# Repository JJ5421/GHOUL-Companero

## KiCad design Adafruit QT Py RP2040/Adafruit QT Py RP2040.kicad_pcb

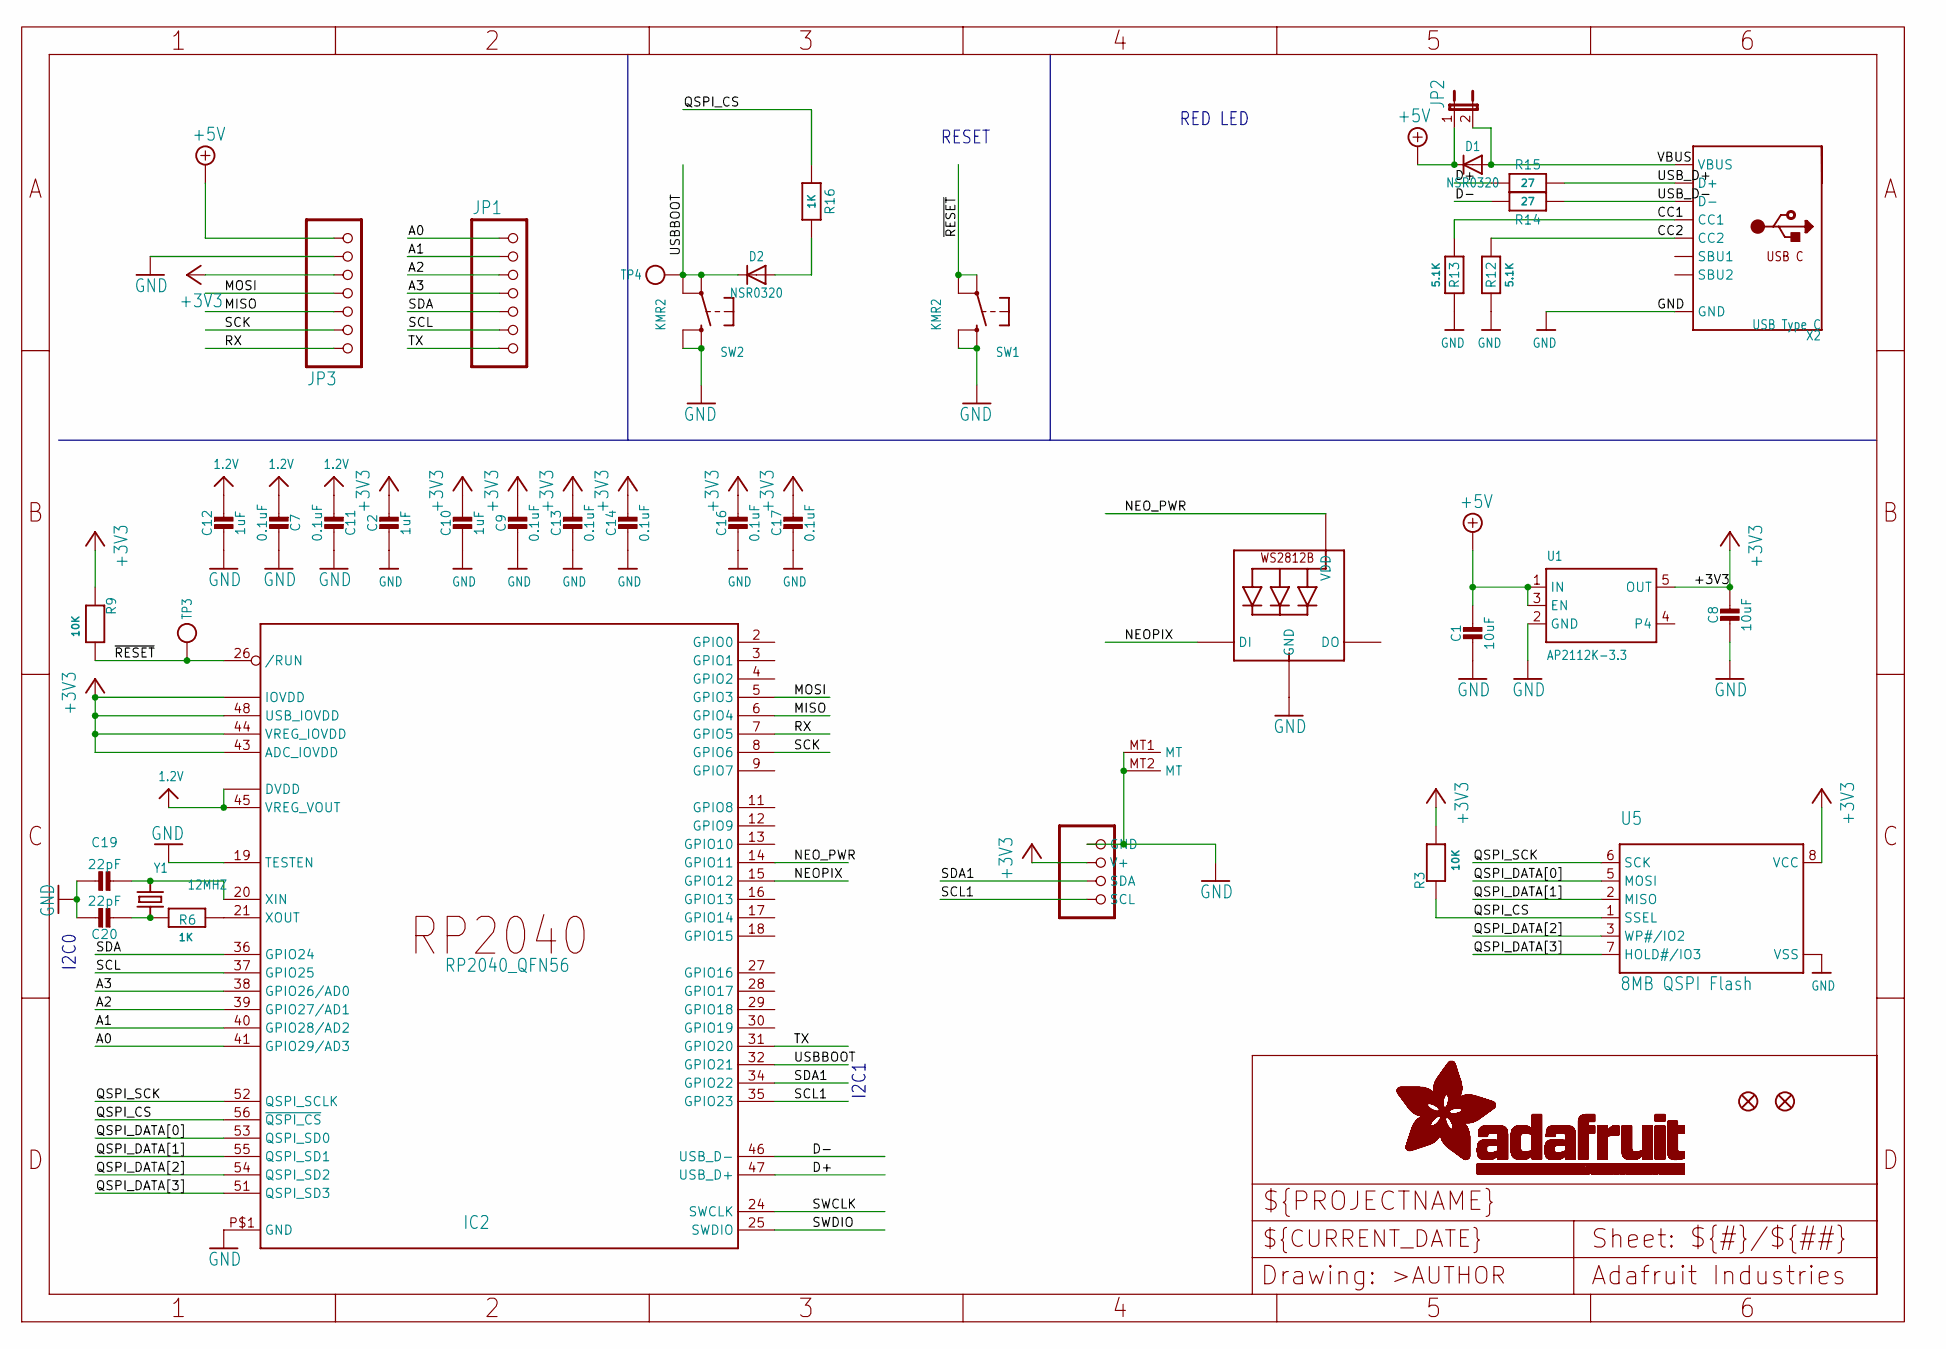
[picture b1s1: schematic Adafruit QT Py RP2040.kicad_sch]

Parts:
C1, C8: 10uF; 0805-NO
C2, C10, C12: 1uF; 0603-NO
C7, C9, C11, C13, C14, C16, C17: 0.1uF; _0402NO
C19, C20: 22pF; _0402NO
CONN1: STEMMA_I2C_QTSKINNY; JST_SH4_SKINNY
D1, D2: NSR0320; SOD-323_MINI
IC2: RP2040_QFN56; QFN56_7MM_REDUCEDEPAD
JP1, JP3: HEADER-1X7_CASTEL; 1X07_CASTEL
JP2: JUMPER-2SMD-NO; SJ_2S-NO
LED1: WS2812B_SK6805_1515; SK6805_1515
R3, R9: 10K; _0402NO
R6, R16: 1K; _0402NO
R12, R13: 5.1K; _0402NO
R14, R15: 27; _0402NO
SW1, SW2: KMR2; BTN_KMR2_4.6X2.8
TP3, TP4: TESTPOINTROUND1.5MMNO; TESTPOINT_ROUND_1.5MM_NO
U1: AP2112K-3.3; SOT23-5
U5: 8MB QSPI Flash; USON8_4X4
U$6, U$8: FIDUCIAL_1MM
X2: USB Type C; USB_C_CUSB31-CFM2AX-01-X
Y1: 12MHZ; CRYSTAL_2.5X2

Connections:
1.2V: C7.2, C11.2, C12.1, IC2.23 (DVDD), IC2.45 (VREG_VOUT), IC2.50 (DVDD)
+3V3: C2.1, C8.1, C9.1, C10.1, C13.1, C14.1, C16.1, C17.1, CONN1.2 (V+), IC2.1 (IOVDD), IC2.10 (IOVDD), IC2.22 (IOVDD), IC2.33 (IOVDD), IC2.42 (IOVDD), IC2.43 (ADC_IOVDD), IC2.44 (VREG_IOVDD), IC2.48 (USB_IOVDD), IC2.49 (IOVDD), JP3.5, JP3.5C (5), R3.2, R9.1, U1.5 (OUT), U5.8 (VCC)
+5V: C1.1, D1.C, JP2.1, JP3.7, JP3.7C (7), U1.1 (IN), U1.3 (EN)
A0: IC2.41 (GPIO29/AD3), JP1.1, JP1.1C (1)
A1: IC2.40 (GPIO28/AD2), JP1.2, JP1.2C (2)
A2: IC2.39 (GPIO27/AD1), JP1.3, JP1.3C (3)
A3: IC2.38 (GPIO26/AD0), JP1.4, JP1.4C (4)
CC1: R13.2, X2.A5 (CC1)
CC2: R12.2, X2.B5 (CC2)
D+: IC2.47 (USB_D+), R15.2
D-: IC2.46 (USB_D-), R14.2
GND: C1.2, C2.2, C7.1, C8.2, C9.2, C10.2, C11.1, C12.2, C13.2, C14.2, C16.2, C17.2, C19.1, C20.1, CONN1.1 (GND), CONN1.MT1 (MT), CONN1.MT2 (MT), IC2.19 (TESTEN), IC2.P$1 (GND), JP3.6, JP3.6C (6), LED1.4 (GND), R12.1, R13.1, SW1.B (S), SW1.B' (S1), SW2.B (S), SW2.B' (S1), U1.2 (GND), U5.4 (VSS), U5.PAD (VSS), X2.A1B12 (GND), X2.B1A12 (GND)
MISO: IC2.6 (GPIO4), JP3.3, JP3.3C (3)
MOSI: IC2.5 (GPIO3), JP3.4, JP3.4C (4)
unnamed: D2.A, R16.2
unnamed: C19.2, IC2.20 (XIN), Y1.3 (2)
unnamed: C20.2, R6.1, Y1.1
unnamed: IC2.21 (XOUT), R6.2
NEOPIX: IC2.15 (GPIO12), LED1.1 (DI)
NEO_PWR: IC2.14 (GPIO11), LED1.2 (VDD)
QSPI_CS: IC2.56 (~QSPI_CS), R3.1, R16.1, U5.1 (SSEL)
QSPI_DATA[0]: IC2.53 (QSPI_SD0), U5.5 (MOSI)
QSPI_DATA[1]: IC2.55 (QSPI_SD1), U5.2 (MISO)
QSPI_DATA[2]: IC2.54 (QSPI_SD2), U5.3 (WP#/IO2)
QSPI_DATA[3]: IC2.51 (QSPI_SD3), U5.7 (HOLD#/IO3)
QSPI_SCK: IC2.52 (QSPI_SCLK), U5.6 (SCK)
RX: IC2.7 (GPIO5), JP3.1, JP3.1C (1)
SCK: IC2.8 (GPIO6), JP3.2, JP3.2C (2)
SCL: IC2.37 (GPIO25), JP1.6, JP1.6C (6)
SCL1: CONN1.4 (SCL), IC2.35 (GPIO23)
SDA: IC2.36 (GPIO24), JP1.5, JP1.5C (5)
SDA1: CONN1.3 (SDA), IC2.34 (GPIO22)
SWCLK: IC2.24 (SWCLK)
SWDIO: IC2.25 (SWDIO)
TX: IC2.31 (GPIO20), JP1.7, JP1.7C (7)
USBBOOT: D2.C, IC2.32 (GPIO21), SW2.A, SW2.A' (P1), TP4.P$1
USB_D+: R15.1, X2.A6 (D+), X2.B6 (D+)
USB_D-: R14.1, X2.A7 (D-), X2.B7 (D-)
VBUS: D1.A, JP2.2, X2.A4B9 (VBUS), X2.B4A9 (VBUS)
~RESET: IC2.26 (/RUN), R9.2, SW1.A, SW1.A' (P1), TP3.P$1

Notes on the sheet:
I2C1
RED LED
RESET
I2C0

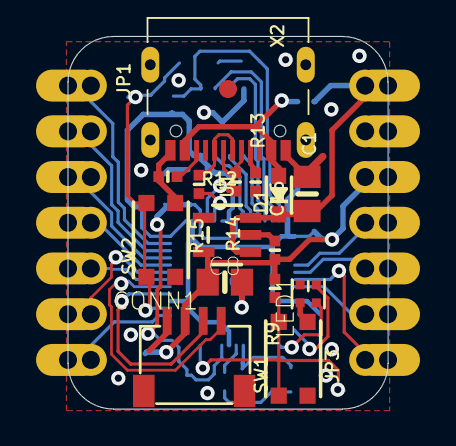
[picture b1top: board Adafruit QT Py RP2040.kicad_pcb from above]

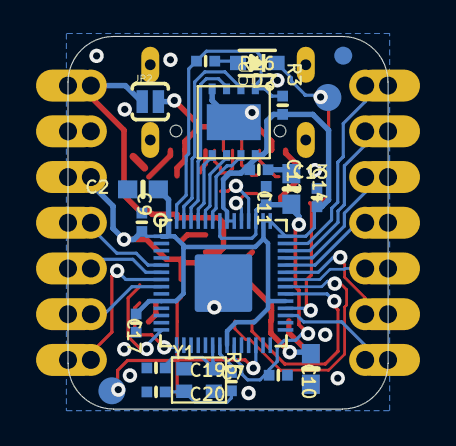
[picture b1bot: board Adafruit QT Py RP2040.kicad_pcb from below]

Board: 16 copper layers, 17.8 x 20.7 mm, 42 parts (23 on the bottom side), 38 nets.

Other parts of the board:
U$1: QTPICO_BOT
U$2: QTPICO_TOP

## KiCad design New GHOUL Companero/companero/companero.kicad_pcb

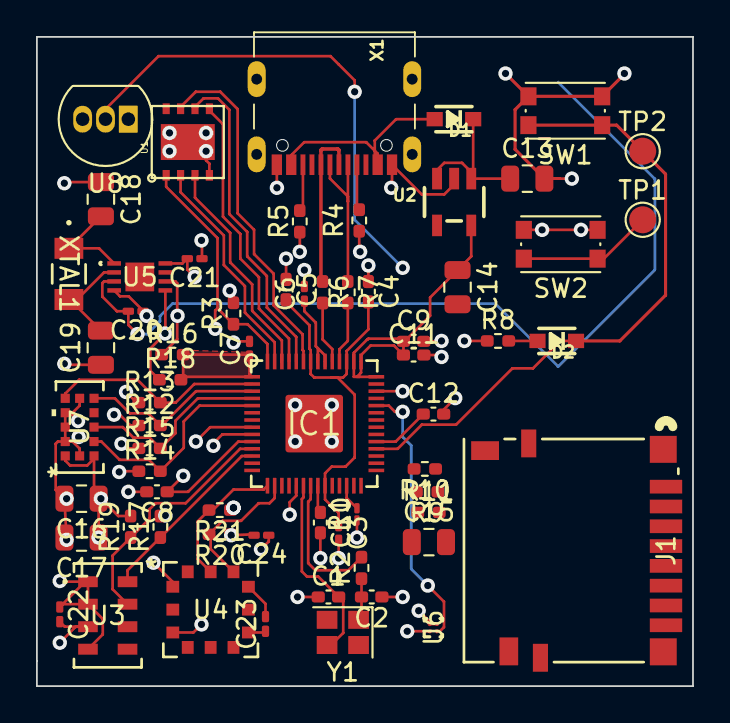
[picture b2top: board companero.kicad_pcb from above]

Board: 4 copper layers, 36.4 x 36.1 mm, 65 parts (1 on the bottom side), 46 nets.

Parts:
BT1: Battery_Cell; BatteryHolder_Keystone_3000_1x12mm
C1, C2: 22pF; C_0402_1005Metric_Pad0.74x0.62mm_HandSolder
C3, C6, C7: 1uF; C_0201_0603Metric_Pad0.64x0.40mm_HandSolder
C4, C5, C8, C9, C10, C11, C12: 0.1uF; C_0402_1005Metric_Pad0.74x0.62mm_HandSolder
C13, C14, C15: 10uF; C_0805_2012Metric
C16: 100nF; C_0805_2012Metric
C17: 4.7uF; C_0805_2012Metric
C18, C19: 14pF; C_0805_2012Metric
C20, C21, C22, C24: 0.1uF; C_0201_0603Metric_Pad0.64x0.40mm_HandSolder
C23: 1nF; C_0201_0603Metric_Pad0.64x0.40mm_HandSolder
D1, D2: NSR0320; SOD-323_MINI
IC1: RP2040_QFN56; QFN56_7MM_REDUCEDEPAD
J1: DM3D-SF; CONN8_DM3D-SF_HIR
R1: 10K; R_01005_0402Metric_Pad0.57x0.30mm_HandSolder
R2, R8: 1K; R_0402_1005Metric_Pad0.72x0.64mm_HandSolder
R3, R9, R10: 10K; R_0402_1005Metric_Pad0.72x0.64mm_HandSolder
R4, R5: 5.1K; R_0402_1005Metric_Pad0.72x0.64mm_HandSolder
R6, R7: 27; R_0402_1005Metric_Pad0.72x0.64mm_HandSolder
R11: DNF; R_0402_1005Metric_Pad0.72x0.64mm_HandSolder
R12, R13, R16, R17, R18, R19, R20, R21: 10k; R_0402_1005Metric_Pad0.72x0.64mm_HandSolder
R14, R15: 1k; R_0402_1005Metric_Pad0.72x0.64mm_HandSolder
SW1, SW2: KMR2; SW_Push_1P1T_NO_CK_KMR2
TP1, TP2: TESTPOINTROUND1.5MMNO; TestPoint_Pad_D1.5mm
U1: 8MB QSPI Flash; USON8_4X4
U2: AP2112K-3.3; SOT23-5
U3: MS560702BA03-50; SON8_MS5611_TEC
U4: MPRLS0025PA00001A; MPRLS_HNW
U5: MCP7940NT-I/MNY; TDFN8_2x3MC_MCH
U6: LMT70YFQR; YFQ0004ACAC
U7: VL53L1CBV0FY/1; QFN_BV0FY&slash_1_STM
U8: DS18B20; TO-92_Inline
X1: USB Type C; USB_C_CUSB31-CFM2AX-01-X
XTAL1: SC32S-7PF20PPM (32.768kHz); XTAL_SC32S-7PF20PPM_EPS
Y1: 12MHZ; Crystal_SMD_2520-4Pin_2.5x2.0mm

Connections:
1.2V: C3.1, C4.2, C5.2, IC1.23 (DVDD), IC1.45 (VREG_VOUT), IC1.50 (DVDD)
5V: C13.1, D1.C, U2.1 (IN), U2.3 (EN)
+3V3: C6.1, C7.1, C8.1, C9.1, C10.1, C11.1, C12.1, C14.1, C15.1, C16.1, C17.1, C21.2, C22.1, C24.2, IC1.1 (IOVDD), IC1.10 (IOVDD), IC1.22 (IOVDD), IC1.33 (IOVDD), IC1.42 (IOVDD), IC1.43 (ADC_IOVDD), IC1.44 (VREG_IOVDD), IC1.48 (USB_IOVDD), IC1.49 (IOVDD), J1.4 (VDD), R1.1, R3.2, R9.2, R10.2, R12.1, R13.1, R14.1, R15.1, R16.2, R17.2, R18.2, R19.2, R20.1, R21.1, U1.8 (VCC), U2.5 (OUT), U3.1 (VDD), U3.2 (PS), U3.4 (CSB), U4.12 (VDD), U5.8 (VCC), U6.A2 (VDD), U6.B2 (T_ON), U7.1 (AVDDVCSEL), U7.11 (AVDD), U8.3 (V_{DD})
/CC1: R4.2, X1.A5 (CC1)
/CC2: R5.2, X1.B5 (CC2)
/D+: IC1.47 (USB_D+), R6.2
/D-: IC1.46 (USB_D-), R7.2
/QSPI_CS: IC1.56 (~QSPI_CS), R3.1, R8.1, U1.1 (SSEL)
/QSPI_DATA[0]: IC1.53 (QSPI_SD0), U1.5 (MOSI)
/QSPI_DATA[1]: IC1.55 (QSPI_SD1), U1.2 (MISO)
/QSPI_DATA[2]: IC1.54 (QSPI_SD2), U1.3 (WP#/IO2)
/QSPI_DATA[3]: IC1.51 (QSPI_SD3), U1.7 (HOLD#/IO3)
/QSPI_SCK: IC1.52 (QSPI_SCLK), U1.6 (SCK)
/USBBOOT: D2.C, IC1.32 (GPIO21), SW1.1, TP2.1
/USB_D+: R6.1, X1.A6 (D+), X1.B6 (D+)
/USB_D-: R7.1, X1.A7 (D-), X1.B7 (D-)
/VBUS: D1.A, X1.A4B9 (VBUS), X1.B4A9 (VBUS)
/~RESET: IC1.26 (/RUN), R1.2, SW2.1, TP1.1
AnalogTemp Data: IC1.38 (GPIO26/AD0), U6.B1 (TA0)
AnalogTemp Data 2: IC1.40 (GPIO28/AD2), U8.2 (DQ)
BMP SCL: IC1.12 (GPIO9), R17.1, U3.8 (SCLK)
BMP SDA: IC1.11 (GPIO8), R19.1, U3.7 (SDI/SDA)
GND: BT1.2 (-), C1.1, C2.1, C3.2, C4.1, C5.1, C6.2, C7.2, C8.2, C9.2, C10.2, C11.2, C12.2, C13.2, C14.2, C15.2, C16.2, C17.2, C18.1, C19.1, C20.1, C21.1, C22.2, C24.1, IC1.19 (TESTEN), IC1.P$1 (GND), J1.6 (VSS), R4.1, R5.1, R11.1, SW1.2 (S1), SW2.2 (S1), U1.4 (VSS), U1.PAD (VSS), U2.2 (GND), U3.3 (GND), U4.10 (VSS), U5.4 (VSS), U6.A1 (GND), U7.2 (AVSSVCSEL), U7.3 (GND), U7.4 (GND2), U7.6 (GND3), U7.12 (GND4), U8.1 (GND), X1.A1B12 (GND), X1.B1A12 (GND)
GPIO5: IC1.7 (GPIO5), J1.5 (CLK), R11.2
GPIO16: IC1.27 (GPIO16), J1.3 (CMD)
GPIO17: IC1.28 (GPIO17), J1.7 (DAT0)
GPIO20: IC1.31 (GPIO20), J1.2 (DAT3/CD)
unnamed: C2.2, R2.1, Y1.1
unnamed: D2.A, R8.2
unnamed: C1.2, IC1.20 (XIN), Y1.3 (2)
unnamed: IC1.21 (XOUT), R2.2
unnamed: C23.2, U4.4 (VO+)
unnamed: C23.1, U4.6 (VO-)
unnamed: C18.2, U5.1 (X1), XTAL1.1
unnamed: C19.2, U5.2 (X2), XTAL1.2
Pressure SCL: IC1.16 (GPIO13), R20.2, U4.3 (SCLK/SCL)
Pressure SDA: IC1.15 (GPIO12), R21.2, U4.2 (MOSI/SDA)
RTC SCL: IC1.9 (GPIO7), R16.1, U5.6 (SCL)
RTC SDA: IC1.8 (GPIO6), R18.1, U5.5 (SDA)
SD_DAT1: IC1.29 (GPIO18), J1.8 (DAT1), R10.1
SD_DAT2: IC1.30 (GPIO19), J1.1 (DAT2), R9.1
ToF SDA: IC1.4 (GPIO2), R15.2, U7.9 (SDA)
ToF GPIO1: IC1.3 (GPIO1), R12.2, U7.7 (GPIO1)
ToF SCL: IC1.5 (GPIO3), R14.2, U7.10 (SCL)
ToF XSHUT: IC1.2 (GPIO0), R13.2, U7.5 (XSHUT)
VBat: BT1.1 (+), C20.2, U5.3 (VBAT)
